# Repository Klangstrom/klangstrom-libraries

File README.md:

# Klangstrom Hardware 

*Klangstrom* (KLST) is a subtractive infrastructure design framework to facilitate generative, networked, embedded sound + music + composition. *klangstrom* is comprised of two software libraries ( *klang* a node+text-based sound synthesis library and *strom* a node+text-based generative composition library ), an embedded hardware platform, and a programming environment to allow seamless development of generative, networked, embedded sound + music + composition applications.

this repository hosts the hardware designs of *Klangstrom* boards:

KLST_PANDA (v1.0a) :: handheld-style development board with audio in-+output, MIDI in-+output, 2 on-board microphones, 4.3" TFT display, SD card reader, 16 MB external memory, 2 encoders, 2 mechanical keys, rechargeable battery ( based on STM32H723ZGT )

KLST_SHEEP (v0.1) :: handheld-style development board with 16 LEDs, 2 encoders, display ( based on STM32H743VI )

KLST_TINY (v0.1) :: pocket-calculator-sized development board with 3 LEDs, 3 encoders ( based on STM32F446RE )

for more information on the project visit [documentations](https://klangstrom-for-arduino.dennisppaul.de) or follow the development process at [Klangstrom Developer Diary](https://klangstrom.dennisppaul.de).

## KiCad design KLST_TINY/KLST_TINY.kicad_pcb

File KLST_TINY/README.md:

# KLANGSTROM / KLST_TINY

KLST_TINY is a small version of the KLST_CORE board:

- featuring *KLANGSTROM* library
- programmable in Arduino IDE via USB ( *DFUse Mode* )
- debugging + communication via *virtual USB Serial Port*

## feature list (20210322)

- STM32F446 MCU with 180MHz, 128KB RAM, 512KB Flash
- WM8731 audio codec with 2× audio DAC + 2× audio ADC ( 16/24BIT )
- 2× ADC ( 12BIT, opt 6 extra channels )
- 2× DAC ( 12BIT )
- 3× UART ( serial )
- 8× GPIO
- 1× USB ( device or host )
- 1× I2C 
- 1× SPI 
- 3× rotary encoders with push buttons ( TIM2, TIM3, TIM8 )
- 3× programmable LEDs + 1× power LED
- 11× timers
- 1× SD card reader
- 1× JTAG/SWD interface ( 10-pin )
- programmer + reset + boot flash buttons
- 4× Mounting Holes

## technical details

### timers

| TIMER | FUNCTION                         |
|-------|----------------------------------|
| TIM1  | (UNUSED)                         |
| TIM2  | ENCODER_02                       |
| TIM3  | ENCODER_00                       |
| TIM4  | (UNUSED)                         |
| TIM5  | BEAT_CALLBACK                    |
| TIM6  | TIMER_TONE                       |
| TIM7  | TIMER_SERVO                      |
| TIM8  | ENCODER_01                       |
| TIM9  | (UNUSED)                         |
| TIM10 | (UNUSED)                         |
| TIM11 | (UNUSED)                         |
| TIM12 | (UNUSED)                         |
| TIM13 | (UNUSED)                         |
| TIM14 | (UNUSED)                         |

#### timer-based PWM alternative PINs

| FUNCTION        | PIN  | TIMER:CHANNEL        |
|-----------------|------|----------------------|
| ADC_00          | PB0  | TIM1:CH2N            |
| ADC_01          | PB1  | TIM1:CH3N            |
| GPIO_05         | PA2  | TIM9:CH1             |
| GPIO_06         | PA3  | TIM9:CH2             |
| I2C_00_SCL      | PB8  | TIM10:CH1 / TIM4:CH3 |
| I2C_00_SDA      | PB7  | TIM4:CH2             |
| SPI_SDCARD_MISO | PB14 | TIM1:CH2N            |
| SPI_SDCARD_MOSI | PB15 | TIM1:CH3N            |
| SPI_SDCARD_SCK  | PB13 | TIM1:CH1N            |
| UART_00_RX      | PA10 | TIM1:CH3             |
| UART_00_TX      | PB6  | TIM4:CH1             |

## PIN assignment

| PIN  | LABEL                       |
|------|-----------------------------|
| PB0  | ADC_00                      |
| PB1  | ADC_01                      |
| PA8  | AUDIOCODEC_I2C_SCL          |
| PC9  | AUDIOCODEC_I2C_SDA          |
| PB9  | AUDIOCODEC_SAI_FS_B         |
| PC0  | AUDIOCODEC_SAI_MCLK_B       |
| PB12 | AUDIOCODEC_SAI_SCK_B        |
| PC1  | AUDIOCODEC_SAI_SD_A         |
| PA9  | AUDIOCODEC_SAI_SD_B         |
| PA4  | DAC_00                      |
| PA5  | DAC_01                      |
| PA6  | ENCODER_00_A                |
| PA7  | ENCODER_00_B                |
| PC4  | ENCODER_00_BUTTON           |
| PC6  | ENCODER_01_A                |
| PC7  | ENCODER_01_B                |
| PC8  | ENCODER_01_BUTTON           |
| PA0  | ENCODER_02_A                |
| PA1  | ENCODER_02_B                |
| PB4  | ENCODER_02_BUTTON           |
| PC13 | GPIO_00                     |
| PC14 | GPIO_01                     |
| PC15 | GPIO_02                     |
| PC2  | GPIO_03                     |
| PC3  | GPIO_04                     |
| PA2  | GPIO_05                     |
| PA3  | GPIO_06                     |
| PC5  | GPIO_07                     |
| PB2  | GPIO_08                     |
| PB10 | GPIO_09                     |
| PB8  | I2C_00_SCL                  |
| PB7  | I2C_00_SDA                  |
| PB5  | LED_00                      |
| PD2  | LED_01                      |
| PC12 | LED_02                      |
| PB14 | SPI_SDCARD_MISO             |
| PB15 | SPI_SDCARD_MOSI             |
| PB13 | SPI_SDCARD_SCK              |
| PA14 | SWD_SWCLK                   |
| PA13 | SWD_SWDIO                   |
| PA15 | SWD_SWI                     |
| PB3  | SWD_SWO                     |
| PA10 | UART_00_RX                  |
| PB6  | UART_00_TX                  |
| PC11 | UART_01_RX                  |
| PC10 | UART_01_TX                  |
| PA11 | USB_DEVICE-                 |
| PA12 | USB_DEVICE+                 |

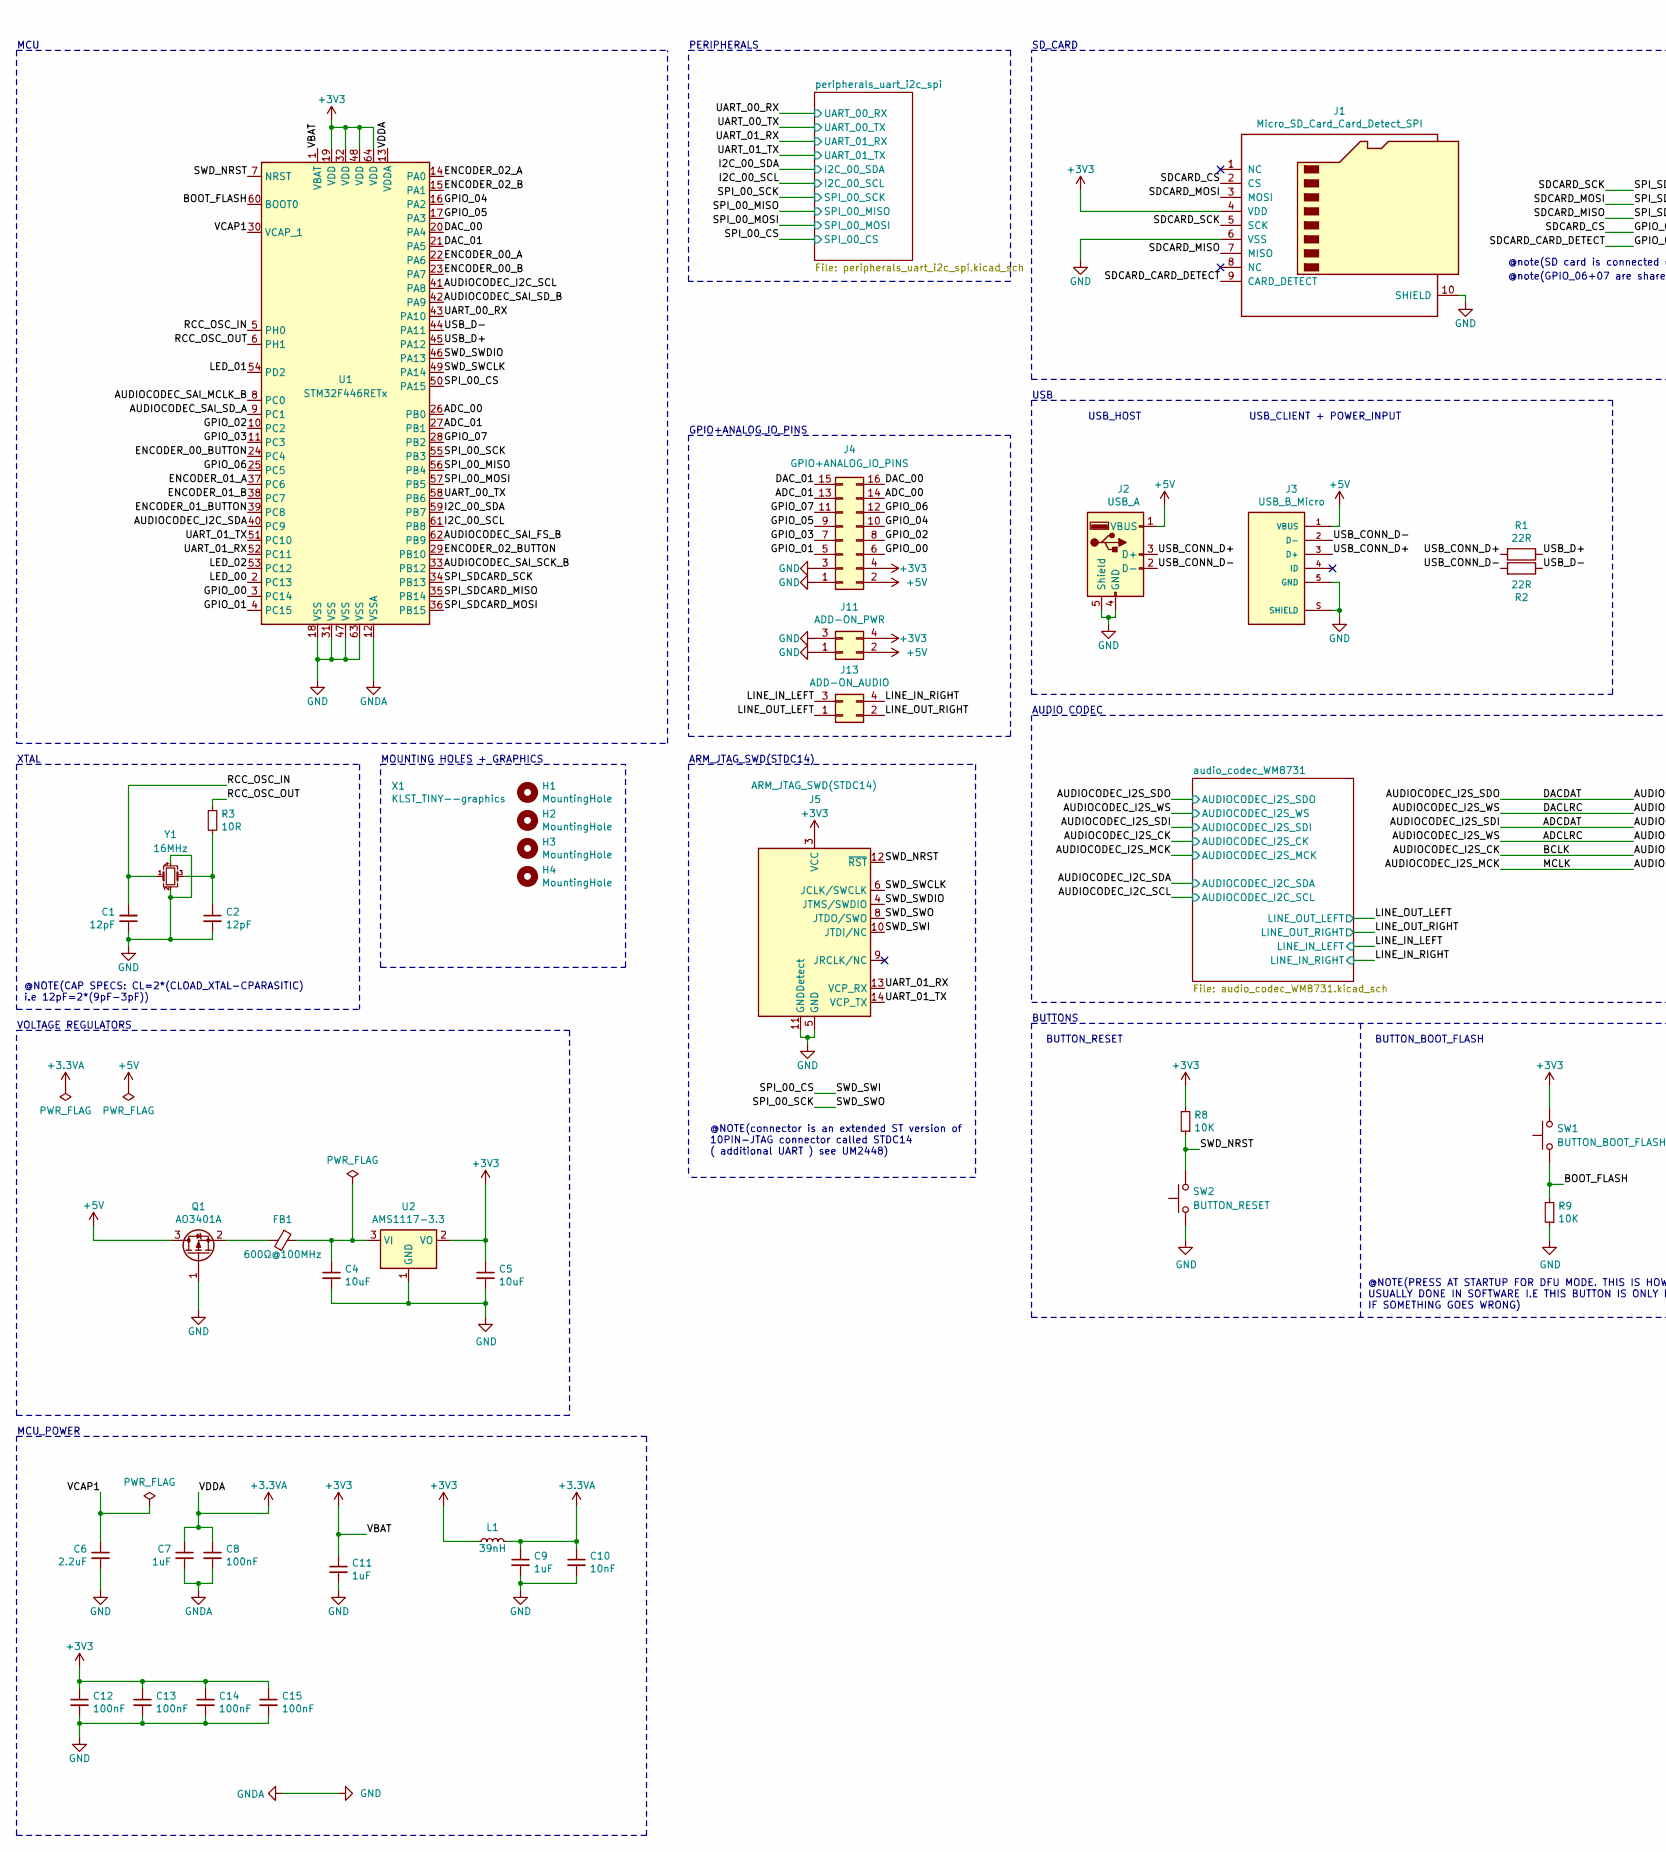
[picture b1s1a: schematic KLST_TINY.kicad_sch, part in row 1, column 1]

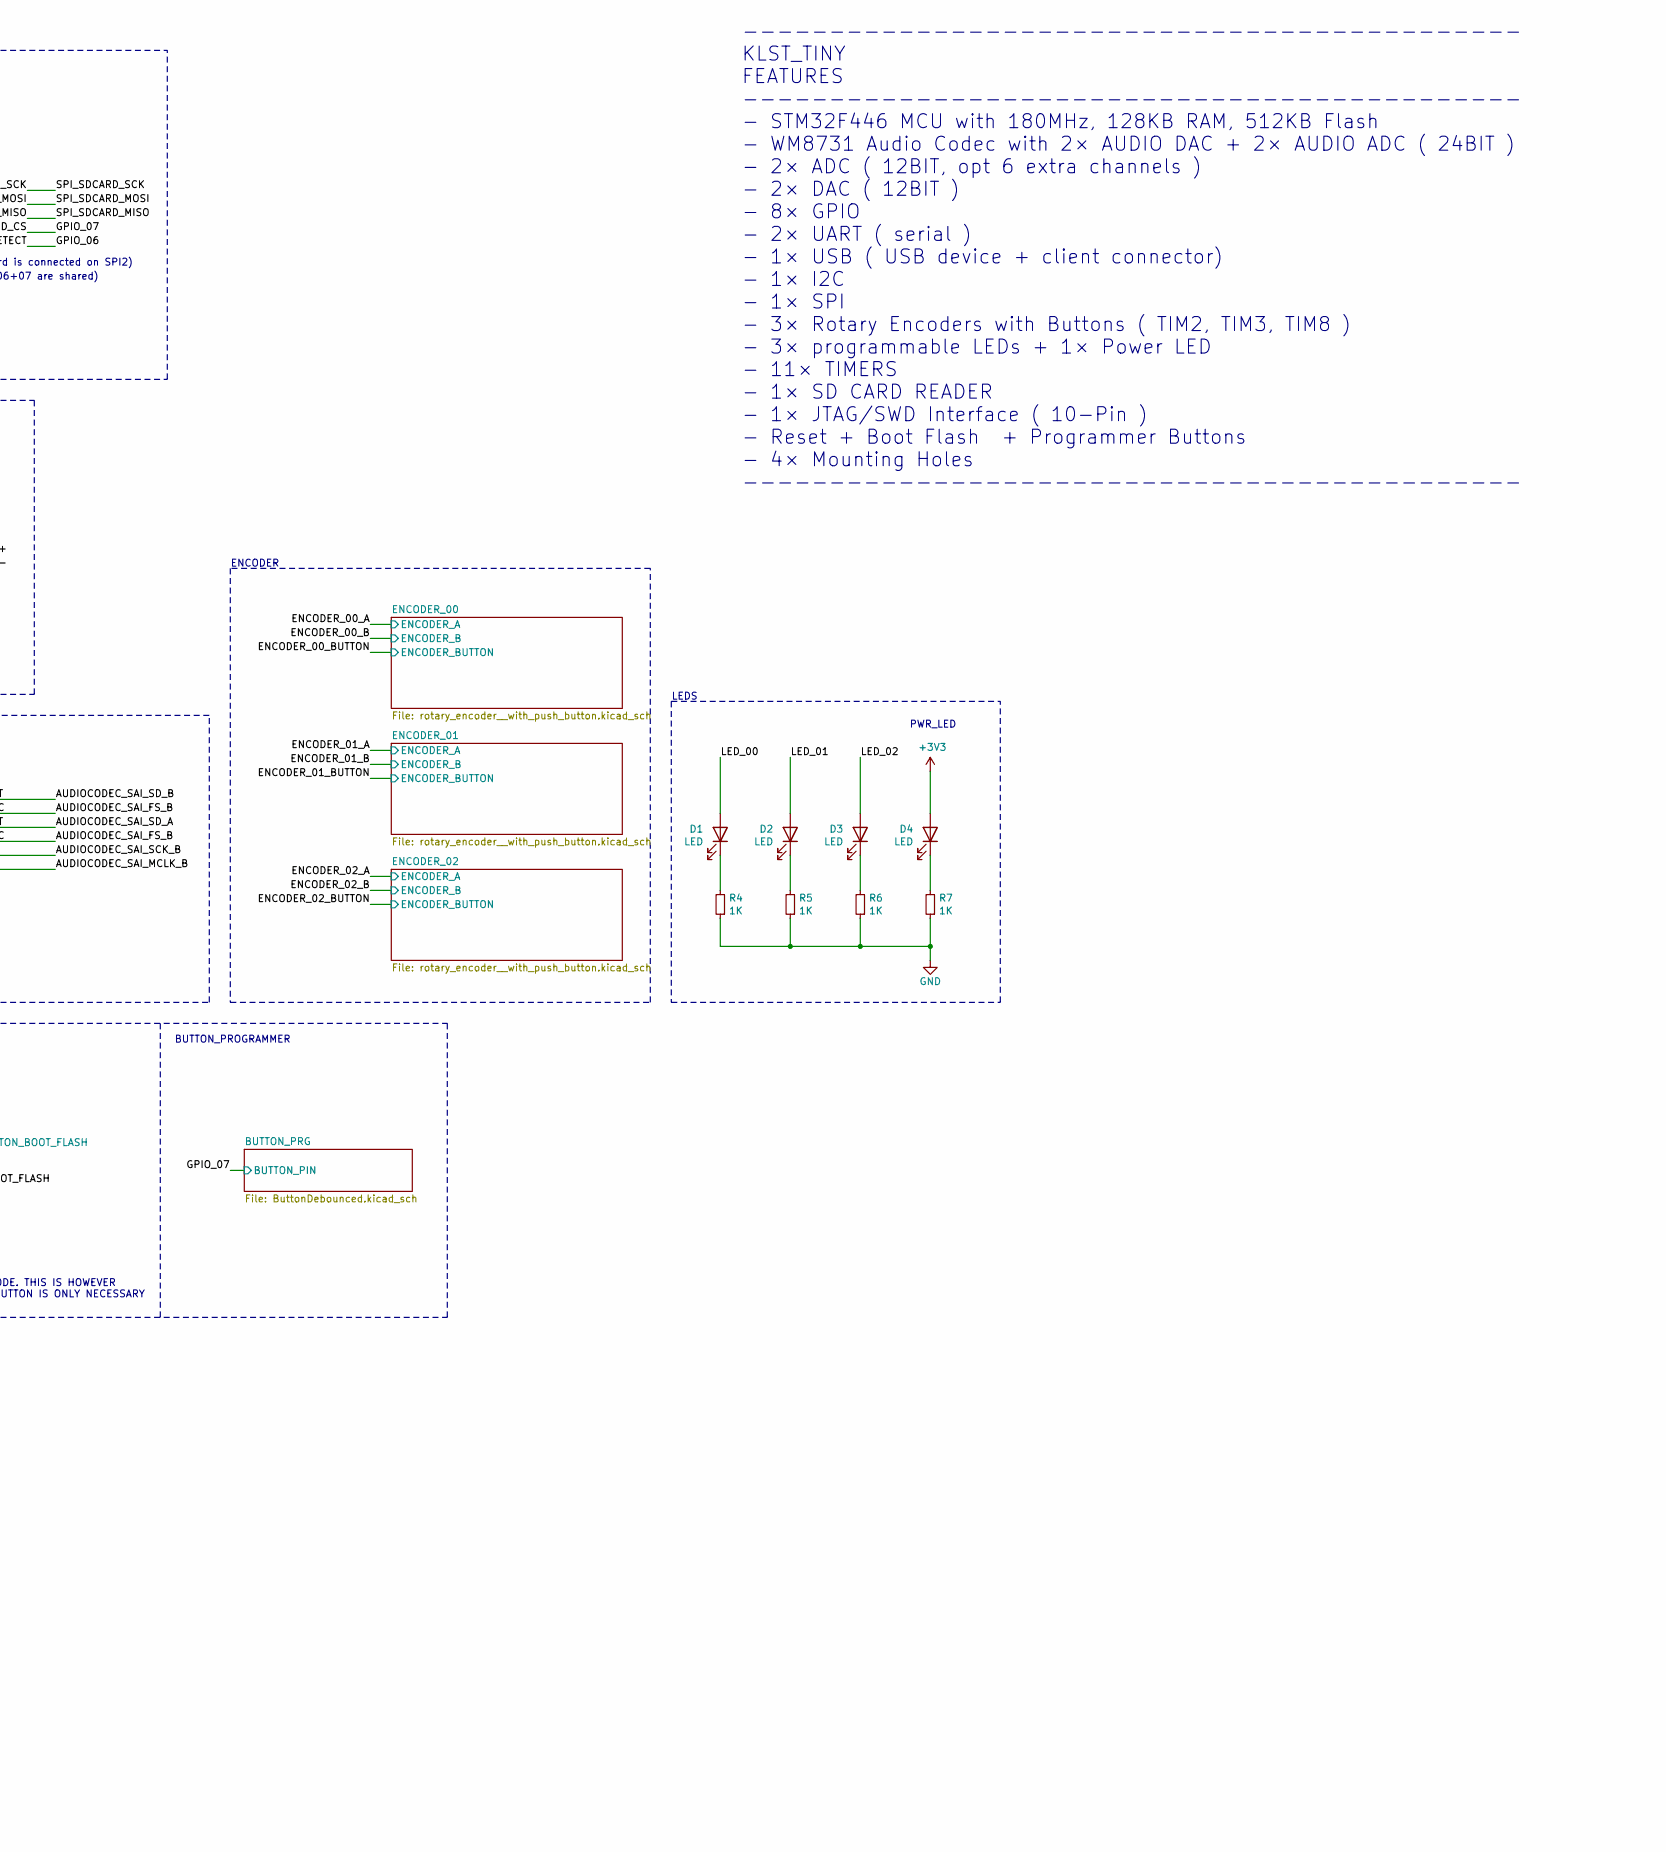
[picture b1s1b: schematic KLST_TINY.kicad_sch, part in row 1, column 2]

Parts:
C1, C2: 12pF; C_0402_1005Metric; MFR.Part # 0402CG120J500NT; LCSC Part # C1547
C4, C5: 10uF; C_0805_2012Metric; MFR.Part # CL21A106KAYNNNE; LCSC Part # C15850
C6: 2.2uF; C_0603_1608Metric; MFR.Part # CL10A225KO8NNNC; LCSC Part # C23630
C7, C9, C11: 1uF; C_0402_1005Metric; MFR.Part # CL05A105KA5NQNC; LCSC Part # C52923
C8, C12, C13, C14, C15: 100nF; C_0402_1005Metric; MFR.Part # CL05B104KO5NNNC; LCSC Part # C1525
C10: 10nF; C_0402_1005Metric; MFR.Part # CL05B103KB5NNNC; LCSC Part # C15195
D1, D2, D3: LED; LED_D3.0mm; MFR.Part # DNF; LCSC Part # DNF
D4: LED; LED_0805_2012Metric_Pad1.15x1.40mm_HandSolder; MFR.Part # C34499; LCSC Part # C34499
FB1: 600Ω@100MHz; L_1206_3216Metric; MFR.Part # CBW321609U601T; LCSC Part # C73732
H1, H2, H3, H4: MountingHole; MountingHole_3.2mm_M3_Pad_Via; MFR.Part # DNF; LCSC Part # DNF
J1: Micro_SD_Card_Card_Detect_SPI; microSD_SOFNG_TF-015; MFR.Part # TF-015; LCSC Part # C113206
J2: USB_A; USB_A_Molex_67643_Horizontal; MFR.Part # 676432911; LCSC Part # C293351
J3: USB_B_Micro; SHOUHAN_MICROXNJ; MFR.Part # MicroXNJ; LCSC Part # C404969
J4: GPIO+ANALOG_IO_PINS; PinHeader_2x08_P2.54mm_Vertical; MFR.Part # DNF; LCSC Part # DNF
J5: ARM_JTAG_SWD(STDC14); PinHeader_2x07_P1.27mm_Vertical_SMD
J11: ADD-ON_PWR; PinHeader_2x02_P2.54mm_Vertical; MFR.Part # DNF; LCSC Part # DNF
J13: ADD-ON_AUDIO; PinHeader_2x02_P2.54mm_Vertical; MFR.Part # DNF; LCSC Part # DNF
L1: 39nH; L_0402_1005Metric; MFR.Part # SDCL1005C39NJTDF; LCSC Part # C26443
Q1: AO3401A; SOT-23; MFR.Part # AO3401A; LCSC Part # C693260
R1, R2: 22R; R_0402_1005Metric; MFR.Part # 0402WGF220JTCE; LCSC Part # C25092
R3: 10R; R_0402_1005Metric; MFR.Part # 0402WGF100JTCE; LCSC Part # C25077
R4, R5, R6, R7: 1K; R_0805_2012Metric_Pad1.20x1.40mm_HandSolder; MFR.Part # 0805W8F1001T5E; LCSC Part # C17513
R8, R9: 10K; R_0402_1005Metric; MFR.Part # 0402WGF1002TCE; LCSC Part # C25744
SW1: BUTTON_BOOT_FLASH; SW_Push_SPST_NO_Alps_SKRK; MFR.Part # SKRKAEE020; LCSC Part # C115357
SW2: BUTTON_RESET; SW_Push_SPST_NO_Alps_SKRK; MFR.Part # SKRKAEE020; LCSC Part # C115357
U1: STM32F446RETx; LQFP-64_10x10mm_P0.5mm; MFR.Part # STM32F446RET6; LCSC Part # C69336
U2: AMS1117-3.3; SOT-223-3_TabPin2; MFR.Part # AMS1117-3.3; LCSC Part # C6186
X1: KLST_TINY--graphics; MFR.Part # DNF; LCSC Part # DNF
Y1: 16MHz; Crystal_SMD_3225-4Pin_3.2x2.5mm; MFR.Part # X322516MLB4SI; LCSC Part # C13738

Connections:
+3.3VA: C7.1, C8.1, C9.1, C10.1, L1.2, U1.13 (VDDA); also elsewhere on the board
+3V3: C5.1, C11.1, C12.1, C13.1, C14.1, C15.1, D4.2 (A), J1.4 (VDD), J4.4, J5.3 (VCC), J11.4, L1.1, R8.2, SW1.2, U1.1 (VBAT), U1.19 (VDD), U1.32 (VDD), U1.48 (VDD), U1.64 (VDD), U2.2 (VO); also elsewhere on the board
+5V: J2.1 (VBUS), J3.1 (VBUS), J4.2, J11.2, Q1.3 (D)
/ADCDAT: U1.9 (PC1); also elsewhere on the board
/ADCLRC: U1.62 (PB9); also elsewhere on the board
/ADC_00: J4.14, U1.26 (PB0)
/ADC_01: J4.13, U1.27 (PB1)
/AUDIOCODEC_I2C_SCL: U1.41 (PA8); also elsewhere on the board
/AUDIOCODEC_I2C_SDA: U1.40 (PC9); also elsewhere on the board
/AUDIOCODEC_I2S_CK: U1.33 (PB12); also elsewhere on the board
/AUDIOCODEC_I2S_MCK: U1.8 (PC0); also elsewhere on the board
/AUDIOCODEC_I2S_SDO: U1.42 (PA9); also elsewhere on the board
/BOOT_FLASH: R9.2, SW1.1, U1.60 (BOOT0)
/DAC_00: J4.16, U1.20 (PA4)
/DAC_01: J4.15, U1.21 (PA5)
/ENCODER_00_A: U1.22 (PA6); also elsewhere on the board
/ENCODER_00_B: U1.23 (PA7); also elsewhere on the board
/ENCODER_00_BUTTON: U1.24 (PC4); also elsewhere on the board
/ENCODER_01_A: U1.37 (PC6); also elsewhere on the board
/ENCODER_01_B: U1.38 (PC7); also elsewhere on the board
/ENCODER_01_BUTTON: U1.39 (PC8); also elsewhere on the board
/ENCODER_02_A: U1.14 (PA0); also elsewhere on the board
/ENCODER_02_B: U1.15 (PA1); also elsewhere on the board
/ENCODER_02_BUTTON: U1.29 (PB10); also elsewhere on the board
/GPIO_00: J4.6, U1.3 (PC14)
/GPIO_01: J4.5, U1.4 (PC15)
/GPIO_02: J4.8, U1.10 (PC2)
/GPIO_03: J4.7, U1.11 (PC3)
/GPIO_04: J4.10, U1.16 (PA2)
/GPIO_05: J4.9, U1.17 (PA3)
/GPIO_06: J1.9 (CARD_DETECT), J4.12, U1.25 (PC5)
/GPIO_07: J1.2 (CS), J4.11, U1.28 (PB2); also elsewhere on the board
/I2C_00_SCL: U1.61 (PB8); also elsewhere on the board
/I2C_00_SDA: U1.59 (PB7); also elsewhere on the board
/LED_00: D1.2 (A), U1.2 (PC13)
/LED_01: D2.2 (A), U1.54 (PD2)
/LED_02: D3.2 (A), U1.53 (PC12)
/LINE_IN_LEFT: J13.3; also elsewhere on the board
/LINE_IN_RIGHT: J13.4; also elsewhere on the board
/LINE_OUT_LEFT: J13.1; also elsewhere on the board
/LINE_OUT_RIGHT: J13.2; also elsewhere on the board
/RCC_OSC_IN: C1.2, U1.5 (PH0), Y1.1
/RCC_OSC_OUT: R3.1, U1.6 (PH1)
/SDCARD_MISO: J1.7 (MISO), U1.35 (PB14)
/SDCARD_MOSI: J1.3 (MOSI), U1.36 (PB15)
/SDCARD_SCK: J1.5 (SCK), U1.34 (PB13)
/SPI_00_CS: J5.10 (JTDI/NC), U1.50 (PA15); also elsewhere on the board
/SPI_00_MISO: U1.56 (PB4); also elsewhere on the board
/SPI_00_MOSI: U1.57 (PB5); also elsewhere on the board
/SPI_00_SCK: J5.8 (JTDO/SWO), U1.55 (PB3); also elsewhere on the board
/SWD_NRST: J5.12 (~RST), R8.1, SW2.2, U1.7 (NRST)
/SWD_SWCLK: J5.6 (JCLK/SWCLK), U1.49 (PA14)
/SWD_SWDIO: J5.4 (JTMS/SWDIO), U1.46 (PA13)
/UART_00_RX: U1.43 (PA10); also elsewhere on the board
/UART_00_TX: U1.58 (PB6); also elsewhere on the board
/UART_01_RX: J5.13 (VCP_RX), U1.52 (PC11); also elsewhere on the board
/UART_01_TX: J5.14 (VCP_TX), U1.51 (PC10); also elsewhere on the board
/USB_CONN_D+: J2.3 (D+), J3.3 (D+), R1.2
/USB_CONN_D-: J2.2 (D-), J3.2 (D-), R2.2
/USB_D+: R1.1, U1.45 (PA12)
/USB_D-: R2.1, U1.44 (PA11)
/VCAP1: C6.1, U1.30 (VCAP_1)
GND: C1.1, C2.2, C4.2, C5.2, C6.2, C7.2, C8.2, C9.2, C10.2, C11.2, C12.2, C13.2, C14.2, C15.2, J1.6 (VSS), J1.10 (SHIELD), J2.4 (GND), J2.5 (Shield), J3.5 (GND), J3.S (SHIELD), J4.1, J4.3, J5.5 (GND), J5.7 (GND), J5.11 (GNDDetect), J11.1, J11.3, Q1.1 (G), R4.1, R5.1, R6.1, R7.1, R9.1, SW2.1, U1.12 (VSSA), U1.18 (VSS), U1.31 (VSS), U1.47 (VSS), U1.63 (VSS), U2.1 (GND), Y1.2, Y1.4; also elsewhere on the board
unnamed: C2.1, R3.2, Y1.3
unnamed: D1.1 (K), R4.2
unnamed: D2.1 (K), R5.2
unnamed: D3.1 (K), R6.2
unnamed: D4.1 (K), R7.2
unnamed: FB1.2, Q1.2 (S)
unnamed: C4.1, FB1.1, U2.3 (VI)

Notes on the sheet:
USB_HOST
PWR_LED
BUTTON_PROGRAMMER
ARM_JTAG_SWD(STDC14)
AUDIO CODEC
BUTTONS
@note(GPIO_06+07 are shared)
PERIPHERALS
USB_CLIENT + POWER_INPUT
ENCODER
XTAL
BUTTON_RESET
USB
MCU_POWER
BUTTON_BOOT_FLASH
SD_CARD
MOUNTING HOLES + GRAPHICS
@note(SD card is connected on SPI2)
MCU
GPIO+ANALOG_IO_PINS
@NOTE(connector is an extended ST version of 10PIN-JTAG connector called STDC14 ( additional UART ) see UM2448)
VOLTAGE REGULATORS
--------------------------------------------- KLST_TINY FEATURES --------------------------------------------- - STM32F446 MCU with 180MHz, 128KB RAM, 512KB Flash - WM8731 Audio Codec with 2× AUDIO DAC + 2× AUDIO ADC ( 24BIT ) - 2× ADC ( 12BIT, opt 6 extra channels ) - 2× DAC ( 12BIT ) - 8× GPIO - 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
@NOTE(PRESS AT STARTUP FOR DFU MODE. THIS IS HOWEVER USUALLY DONE IN SOFTWARE I.E THIS BUTTON IS ONLY NECESSARY IF SOMETHING GOES WRONG)
@NOTE(CAP SPECS: CL=2*(CLOAD_XTAL-CPARASITIC) i.e 12pF=2*(9pF-3pF))
LEDS

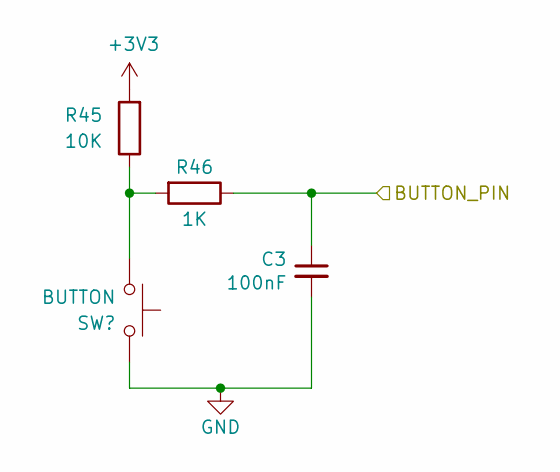
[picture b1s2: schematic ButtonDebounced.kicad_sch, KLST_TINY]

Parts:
C3: 100nF; C_0402_1005Metric; MFR.Part # CL05B104KO5NNNC; LCSC Part # C1525
R45: 10K; R_0402_1005Metric; MFR.Part # 0402WGF1002TCE; LCSC Part # C25744
R46: 1K; R_0402_1005Metric; MFR.Part # 0402WGF1001TCE; LCSC Part # C11702
SW6: BUTTON; SW_Push_SPST_NO_Alps_SKRK; MFR.Part # SKRKAEE020; LCSC Part # C115357

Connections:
+3V3: R45.2; also elsewhere on the board
/GPIO_07: C3.1, R46.1; also elsewhere on the board
GND: C3.2, SW6.2; also elsewhere on the board
unnamed: R45.1, R46.2, SW6.1

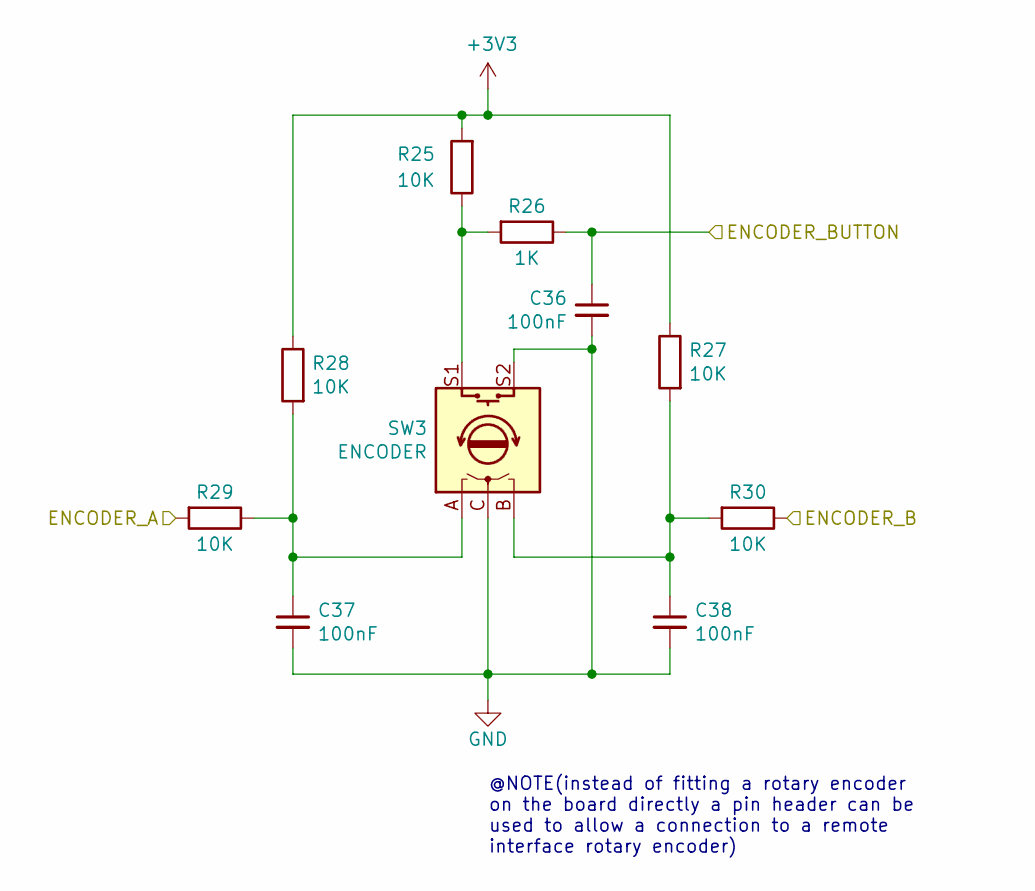
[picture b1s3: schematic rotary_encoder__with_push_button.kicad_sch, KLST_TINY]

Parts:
C36, C37, C38: 100nF; C_0402_1005Metric; MFR.Part # CL05B104KO5NNNC; LCSC Part # C1525
R25, R27, R28, R29, R30: 10K; R_0402_1005Metric; MFR.Part # 0402WGF1002TCE; LCSC Part # C25744
R26: 1K; R_0402_1005Metric; MFR.Part # 0402WGF1001TCE; LCSC Part # C11702
SW3: ENCODER; RotaryEncoder_Alps_EC12E-Switch_Vertical_H20mm; MFR.Part # DNF; LCSC Part # DNF

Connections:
+3V3: R25.2, R27.1, R28.1; also elsewhere on the board
/ENCODER_00_A: R29.2; also elsewhere on the board
/ENCODER_00_B: R30.1; also elsewhere on the board
/ENCODER_00_BUTTON: C36.1, R26.1; also elsewhere on the board
GND: C36.2, C37.2, C38.2, SW3.C, SW3.S2; also elsewhere on the board
unnamed: C37.1, R28.2, R29.1, SW3.A
unnamed: C38.1, R27.2, R30.2, SW3.B
unnamed: R25.1, R26.2, SW3.S1

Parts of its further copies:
C39, C40, C41, C42, C43, C44: 100nF; C_0402_1005Metric; MFR.Part # CL05B104KO5NNNC; LCSC Part # C1525
R31, R33, R34, R35, R36, R37, R39, R40, R41, R42: 10K; R_0402_1005Metric; MFR.Part # 0402WGF1002TCE; LCSC Part # C25744
R32, R38: 1K; R_0402_1005Metric; MFR.Part # 0402WGF1001TCE; LCSC Part # C11702
SW4, SW5: ENCODER; RotaryEncoder_Alps_EC12E-Switch_Vertical_H20mm; MFR.Part # DNF; LCSC Part # DNF

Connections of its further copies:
+3V3: R31.2, R33.1, R34.1, R37.2, R39.1, R40.1; also elsewhere on the board
/ENCODER_01_A: R35.2; also elsewhere on the board
/ENCODER_01_B: R36.1; also elsewhere on the board
/ENCODER_01_BUTTON: C39.1, R32.1; also elsewhere on the board
/ENCODER_02_A: R41.2; also elsewhere on the board
/ENCODER_02_B: R42.1; also elsewhere on the board
/ENCODER_02_BUTTON: C42.1, R38.1; also elsewhere on the board
GND: C39.2, C40.2, C41.2, C42.2, C43.2, C44.2, SW4.C, SW4.S2, SW5.C, SW5.S2; also elsewhere on the board
unnamed: C40.1, R34.2, R35.1, SW4.A
unnamed: C41.1, R33.2, R36.2, SW4.B
unnamed: C43.1, R40.2, R41.1, SW5.A
unnamed: C44.1, R39.2, R42.2, SW5.B
unnamed: R31.1, R32.2, SW4.S1
unnamed: R37.1, R38.2, SW5.S1

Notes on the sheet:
@NOTE(instead of fitting a rotary encoder on the board directly a pin header can be used to allow a connection to a remote interface rotary encoder)

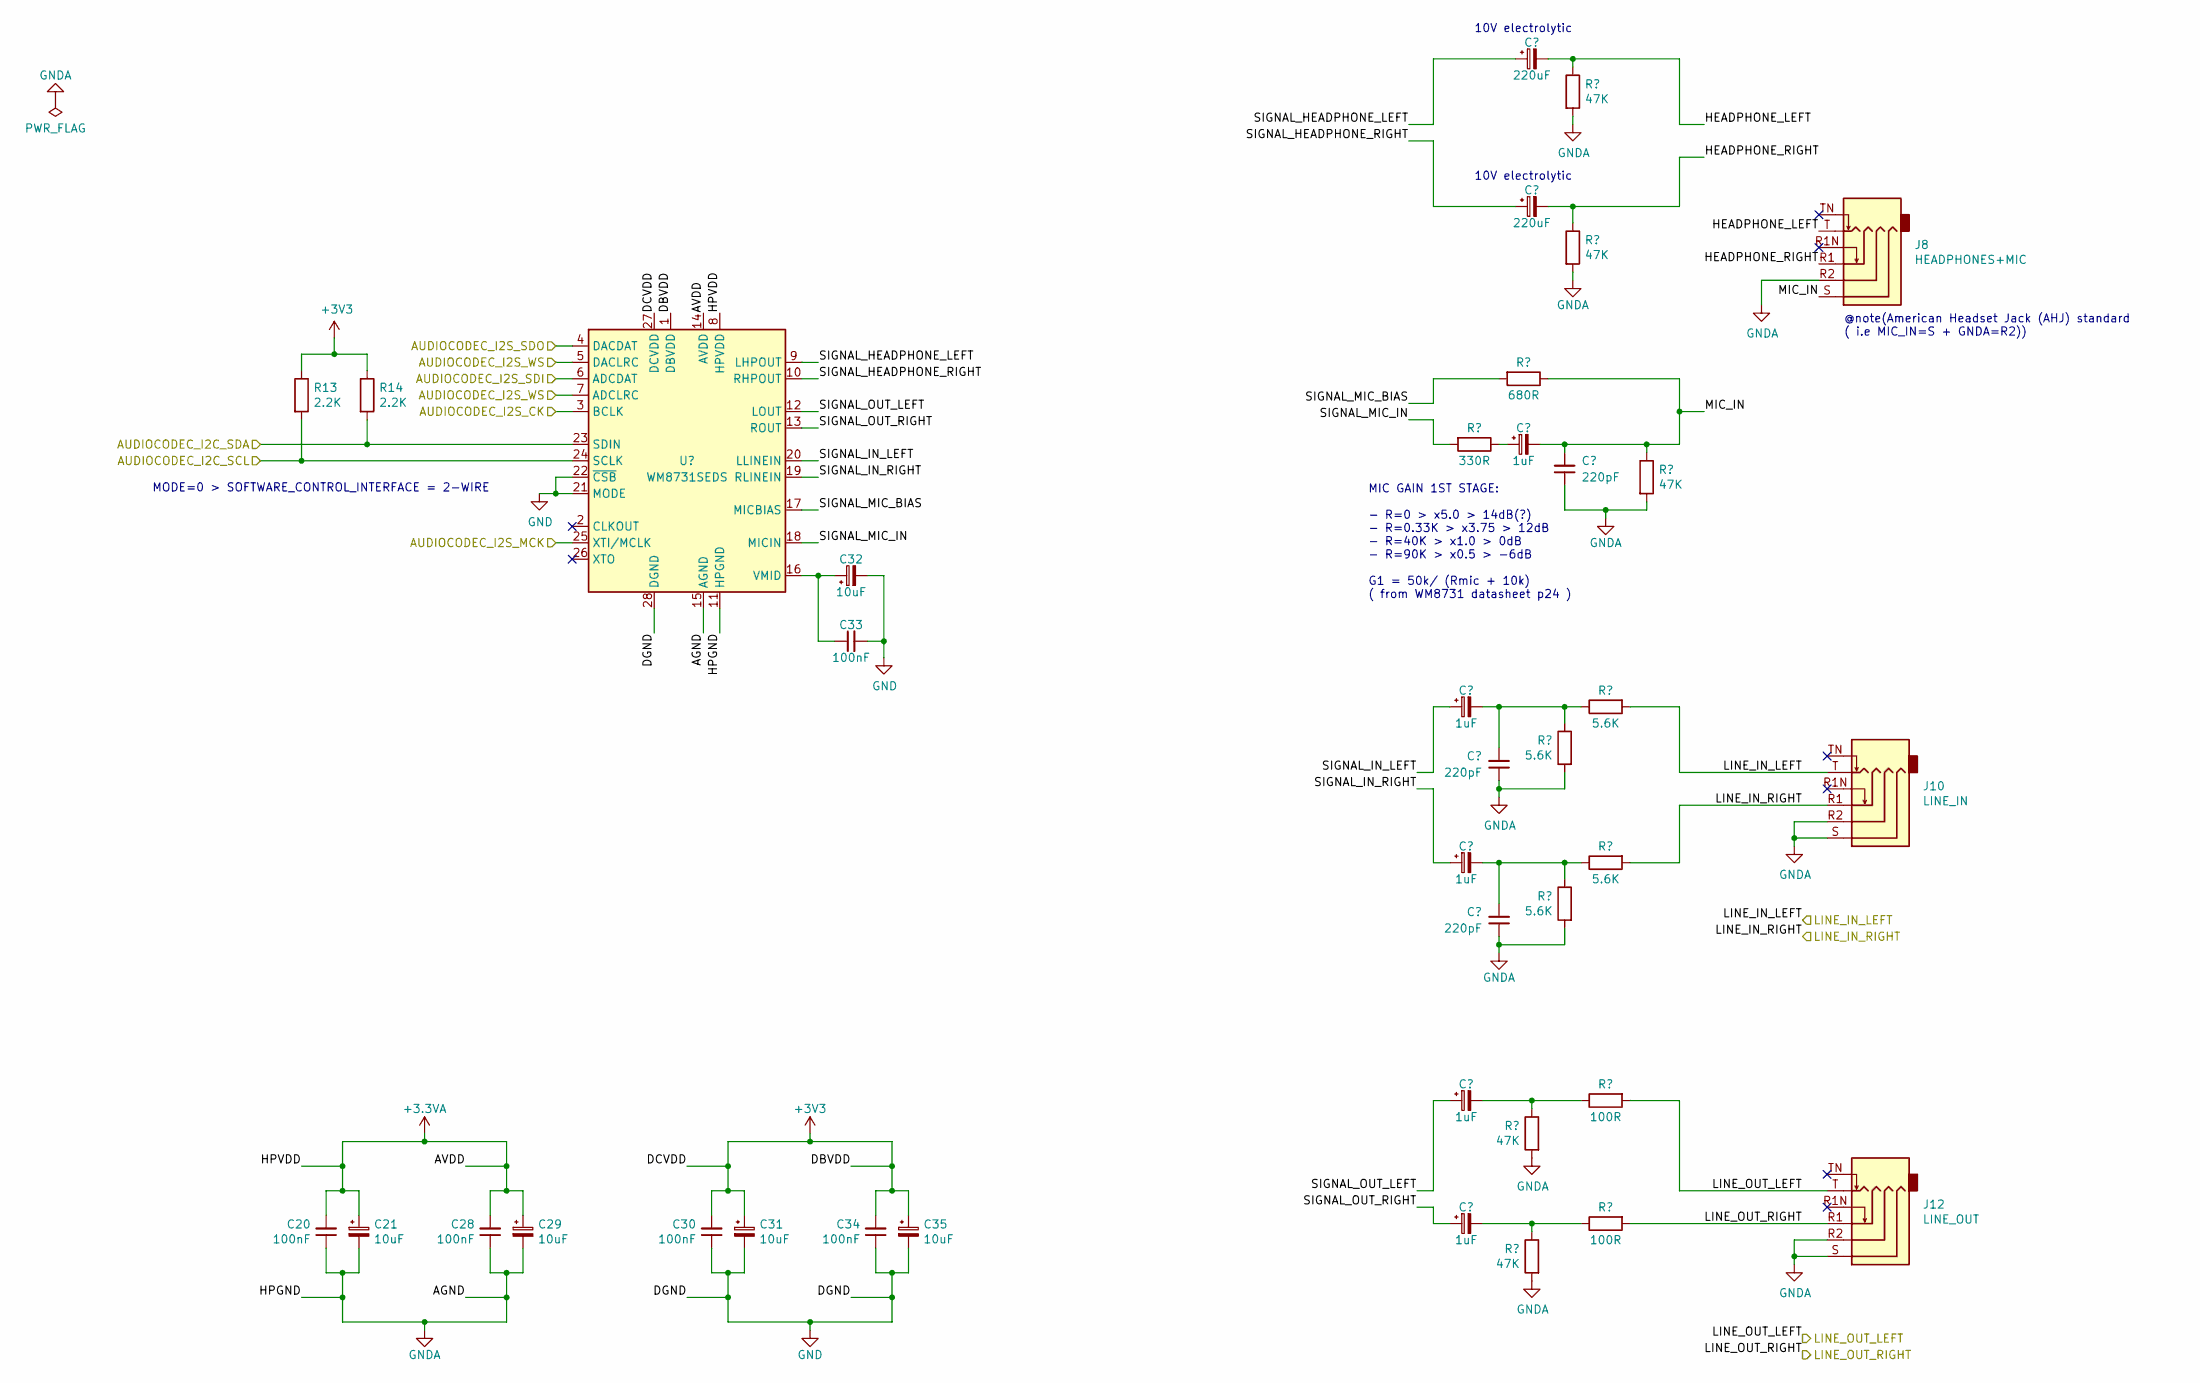
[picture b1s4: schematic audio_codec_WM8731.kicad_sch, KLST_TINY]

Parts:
C16, C17: 220uF; CP_Elec_6.3x5.4; MFR.Part # RVT1A221M0605; LCSC Part # C3345
C18, C22, C24, C26, C27: 1uF; CP_EIA-3216-18_Kemet-A; MFR.Part # TAJA105K025RNJ; LCSC Part # C7175
C19, C23, C25: 220pF; C_0805_2012Metric; MFR.Part # CL21B221KBANNNC; LCSC Part # C53172
C20, C28, C30, C33, C34: 100nF; C_0402_1005Metric; MFR.Part # CL05B104KO5NNNC; LCSC Part # C1525
C21, C29, C31, C32, C35: 10uF; CP_EIA-3216-18_Kemet-A; MFR.Part # TAJA106K016RNJ; LCSC Part # C7171
J8: HEADPHONES+MIC; Korean_Hroparts_Elec_PJ-316A-6A; MFR.Part # PJ-316A-6A; LCSC Part # C128987
J10: LINE_IN; Korean_Hroparts_Elec_PJ-316A-6A; MFR.Part # PJ-316A-6A; LCSC Part # C128987
J12: LINE_OUT; Korean_Hroparts_Elec_PJ-316A-6A; MFR.Part # PJ-316A-6A; LCSC Part # C128987
R10, R11, R16, R22, R24: 47K; R_0805_2012Metric; MFR.Part # 0805W8F4702T5E; LCSC Part # C17713
R12: 680R; R_0805_2012Metric; MFR.Part # 0805W8F6800T5E; LCSC Part # C17798
R13, R14: 2.2K; R_0402_1005Metric; MFR.Part # 0402WGF2201TCE; LCSC Part # C25879
R15: 330R; R_0805_2012Metric_Pad1.20x1.40mm_HandSolder; MFR.Part # 0805W8F3300T5E; LCSC Part # C17630
R17, R18, R19, R20: 5.6K; R_0805_2012Metric; MFR.Part # 0805W8F5601T5E; LCSC Part # C4382
R21, R23: 100R; R_0805_2012Metric; MFR.Part # 0805W8F1000T5E; LCSC Part # C17408
U3: WM8731SEDS; SSOP-28_5.3x10.2mm_P0.65mm; MFR.Part # WM8731SEDS/RV; LCSC Part # C323837

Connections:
+3.3VA: C20.2, C21.1, C28.2, C29.1, U3.8 (HPVDD), U3.14 (AVDD); also elsewhere on the board
+3V3: C30.2, C31.1, C34.2, C35.1, R13.1, R14.1, U3.1 (DBVDD), U3.27 (DCVDD); also elsewhere on the board
/ADCDAT: U3.6 (ADCDAT); also elsewhere on the board
/ADCLRC: U3.5 (DACLRC), U3.7 (ADCLRC); also elsewhere on the board
/AUDIOCODEC_I2C_SCL: R13.2, U3.24 (SCLK); also elsewhere on the board
/AUDIOCODEC_I2C_SDA: R14.2, U3.23 (SDIN); also elsewhere on the board
/AUDIOCODEC_I2S_CK: U3.3 (BCLK); also elsewhere on the board
/AUDIOCODEC_I2S_MCK: U3.25 (XTI/MCLK); also elsewhere on the board
/AUDIOCODEC_I2S_SDO: U3.4 (DACDAT); also elsewhere on the board
/LINE_IN_LEFT: J10.T, R17.2; also elsewhere on the board
/LINE_IN_RIGHT: J10.R1, R19.2; also elsewhere on the board
/LINE_OUT_LEFT: J12.T, R21.2; also elsewhere on the board
/LINE_OUT_RIGHT: J12.R1, R23.2; also elsewhere on the board
/audio_codec_WM8731/HEADPHONE_LEFT: C16.2, J8.T, R10.1
/audio_codec_WM8731/HEADPHONE_RIGHT: C17.2, J8.R1, R11.1
/audio_codec_WM8731/MIC_IN: C18.2, C19.2, J8.S, R12.1, R16.1
/audio_codec_WM8731/SIGNAL_HEADPHONE_LEFT: C16.1, U3.9 (LHPOUT)
/audio_codec_WM8731/SIGNAL_HEADPHONE_RIGHT: C17.1, U3.10 (RHPOUT)
/audio_codec_WM8731/SIGNAL_IN_LEFT: C22.1, U3.20 (LLINEIN)
/audio_codec_WM8731/SIGNAL_IN_RIGHT: C24.1, U3.19 (RLINEIN)
/audio_codec_WM8731/SIGNAL_MIC_BIAS: R12.2, U3.17 (MICBIAS)
/audio_codec_WM8731/SIGNAL_MIC_IN: R15.2, U3.18 (MICIN)
/audio_codec_WM8731/SIGNAL_OUT_LEFT: C26.1, U3.12 (LOUT)
/audio_codec_WM8731/SIGNAL_OUT_RIGHT: C27.1, U3.13 (ROUT)
GND: C19.1, C20.1, C21.2, C23.1, C25.1, C28.1, C29.2, C30.1, C31.2, C32.2, C33.2, C34.1, C35.2, J8.R2, J10.R2, J10.S, J12.R2, J12.S, R10.2, R11.2, R16.2, R18.2, R20.2, R22.2, R24.2, U3.11 (HPGND), U3.15 (AGND), U3.21 (MODE), U3.22 (~CSB), U3.28 (DGND); also elsewhere on the board
unnamed: C18.1, R15.1
unnamed: C22.2, C23.2, R17.1, R18.1
unnamed: C24.2, C25.2, R19.1, R20.1
unnamed: C26.2, R21.1, R22.1
unnamed: C27.2, R23.1, R24.1
unnamed: C32.1, C33.1, U3.16 (VMID)

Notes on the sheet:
MODE=0 > SOFTWARE_CONTROL_INTERFACE = 2-WIRE
10V electrolytic
@note(American Headset Jack (AHJ) standard ( i.e MIC_IN=S + GNDA=R2))
MIC GAIN 1ST STAGE: - R=0 > x5.0 > 14dB(?) - R=0.33K > x3.75 > 12dB - R=40K > x1.0 > 0dB - R=90K > x0.5 > -6dB G1 = 50k/ (Rmic + 10k) ( from WM8731 datasheet p24 )

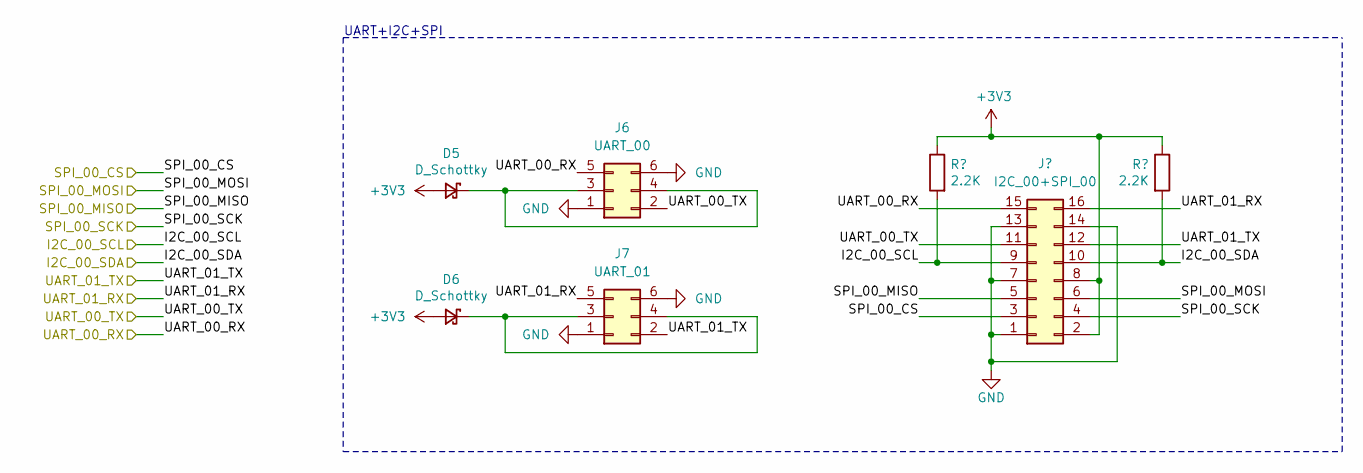
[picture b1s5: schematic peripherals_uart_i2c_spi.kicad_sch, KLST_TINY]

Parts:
D5, D6: D_Schottky; D_SOD-123; MFR.Part # B5819W; LCSC Part # C8598
J6: UART_00; IDC-Header_2x03_P2.54mm_Horizontal; MFR.Part # 300R-6P; LCSC Part # C146629
J7: UART_01; IDC-Header_2x03_P2.54mm_Horizontal; MFR.Part # 300R-6P; LCSC Part # C146629
J9: I2C_00+SPI_00; PinHeader_2x08_P2.54mm_Vertical; MFR.Part # DNF; LCSC Part # DNF
R43, R44: 2.2K; R_0402_1005Metric; MFR.Part # 0402WGF2201TCE; LCSC Part # C25879

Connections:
+3V3: D5.2 (A), D6.2 (A), J9.2, J9.8, R43.1, R44.1; also elsewhere on the board
/I2C_00_SCL: J9.9, R44.2; also elsewhere on the board
/I2C_00_SDA: J9.10, R43.2; also elsewhere on the board
/SPI_00_CS: J9.3; also elsewhere on the board
/SPI_00_MISO: J9.5; also elsewhere on the board
/SPI_00_MOSI: J9.6; also elsewhere on the board
/SPI_00_SCK: J9.4; also elsewhere on the board
/UART_00_RX: J6.5, J9.15; also elsewhere on the board
/UART_00_TX: J6.2, J9.11; also elsewhere on the board
/UART_01_RX: J7.5, J9.16; also elsewhere on the board
/UART_01_TX: J7.2, J9.12; also elsewhere on the board
GND: J6.1, J6.6, J7.1, J7.6, J9.1, J9.7, J9.13, J9.14; also elsewhere on the board
unnamed: D5.1 (K), J6.3, J6.4
unnamed: D6.1 (K), J7.3, J7.4

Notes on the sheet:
UART+I2C+SPI
